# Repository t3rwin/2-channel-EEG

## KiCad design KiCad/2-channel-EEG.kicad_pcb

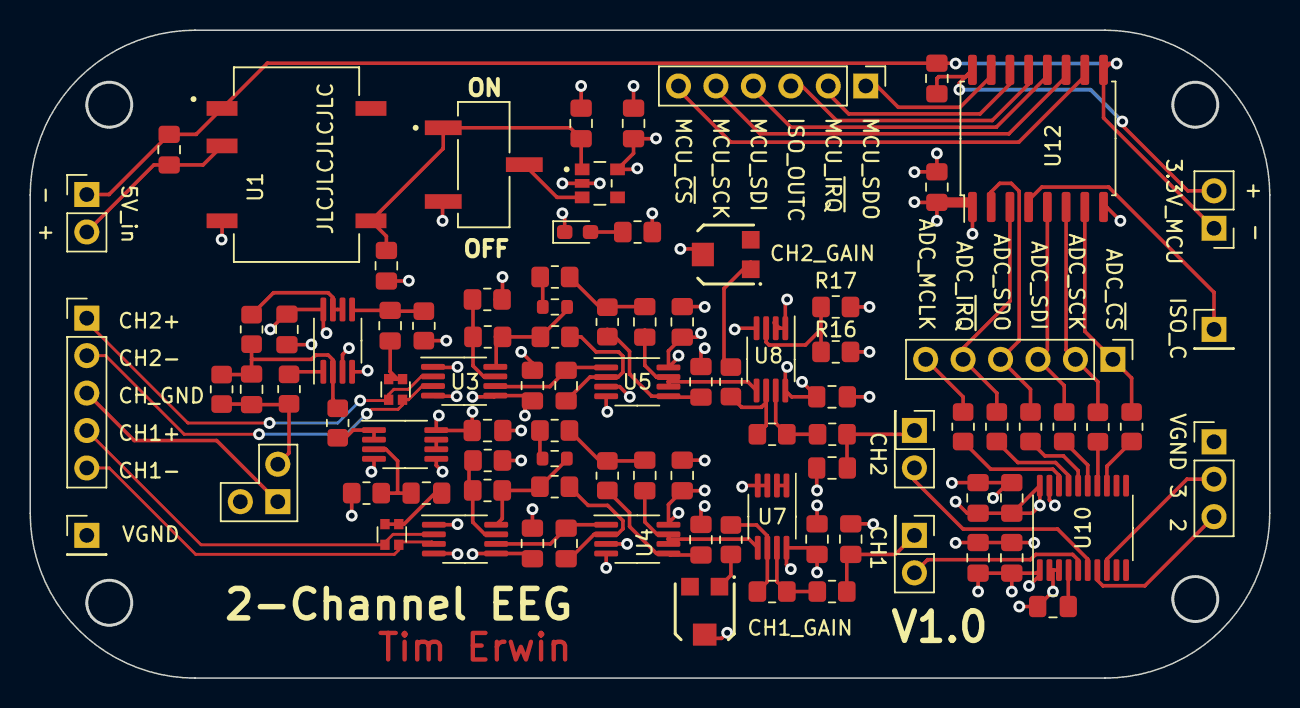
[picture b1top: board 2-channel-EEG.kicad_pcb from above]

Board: 4 copper layers, 84.0 x 43.8 mm, 92 parts (0 on the bottom side), 74 nets.

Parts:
C1: 4.7u; C_0805_2012Metric_Pad1.18x1.45mm_HandSolder
C2, C3, C7, C8, C9, C10, C11, C15, C18, C21, C23, C24, C26, C27, C30: 0.1u; C_0805_2012Metric_Pad1.18x1.45mm_HandSolder
C4, C5, C6, C16, C17, C19, C20, C25: 10u; C_0805_2012Metric_Pad1.18x1.45mm_HandSolder
C12, C28, C29: 1u; C_0805_2012Metric_Pad1.18x1.45mm_HandSolder
C13, C14: 47n; C_0805_2012Metric_Pad1.18x1.45mm_HandSolder
C22: 1n; C_0805_2012Metric_Pad1.18x1.45mm_HandSolder
D1: LED_0603_1608Metric_Pad1.05x0.95mm_HandSolder
J1: Power_Input; PinHeader_1x02_P2.54mm_Vertical
J2: Nucleo_3.3; PinHeader_1x02_P2.54mm_Vertical
J3: Electrode_Input; PinHeader_1x05_P2.54mm_Vertical
J4: GND_select; PinHeader_2x02_P2.54mm_Vertical
J5, J6: Conn_02x01; PinHeader_2x01_P2.54mm_Vertical
J7: VGND; PinHeader_1x01_P2.54mm_Vertical
J8: Conn_01x03; PinHeader_1x03_P2.54mm_Vertical
J9: ADC_Data; PinHeader_1x06_P2.54mm_Vertical
J10: ISO_IN_C; PinHeader_1x01_P2.54mm_Vertical
J11: MCU_Data; PinHeader_1x06_P2.54mm_Vertical
JP1, JP2: SolderJumper_2_Open; R_0603_1608Metric
R1, R3, R21, R30, R31: 1M; R_0805_2012Metric_Pad1.20x1.40mm_HandSolder
R2, R4: 1K; R_0805_2012Metric_Pad1.20x1.40mm_HandSolder
R5, R6: 3M; R_0805_2012Metric_Pad1.20x1.40mm_HandSolder
R7, R8, R9, R10: 56.2k; R_0805_2012Metric_Pad1.20x1.40mm_HandSolder
R11: 510; R_0805_2012Metric_Pad1.20x1.40mm_HandSolder
R12, R13: 1k; R_0805_2012Metric_Pad1.20x1.40mm_HandSolder
R14, R15: 100k; R_0805_2012Metric_Pad1.20x1.40mm_HandSolder
R16, R17, R22, R23: 10k; R_0805_2012Metric_Pad1.20x1.40mm_HandSolder
R18, R19: 100; R_0805_2012Metric_Pad1.20x1.40mm_HandSolder
R20: 0; R_0805_2012Metric_Pad1.20x1.40mm_HandSolder
R24, R25, R26, R27, R28, R29: 10; R_0805_2012Metric_Pad1.20x1.40mm_HandSolder
RN1, RN2: Matched_10K_Resistor_Array_2x; R_Array_Matched_2x0606
RV1, RV2: 10k; TRIM_35WR10KLFTR
SW1: SW_Push_SPDT; SW_JS102011SCQN
U1: PESE1-S5-S5-M-TR; CONV_PESE1-S5-S5-M
U2, U3: AD8237; MSOP-8_3x3mm_P0.65mm
U4, U5, U7, U8, U9, U11: AD8606; MSOP-8_3x3mm_P0.65mm
U6: TCR2EF33; IC_TC4S584F_LF
U10: MCP3562R; TSSOP-20_4.4x6.5mm_P0.65mm
U12: ISO6763-Q1; SOIC-16W_7.5x10.3mm_P1.27mm

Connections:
+3.3V: C2.2, C3.2, C7.2, C8.2, C12.2, C15.1, C18.1, C20.2, C21.2, C23.2, C24.2, C25.2, C26.2, C27.1, R11.2, R16.2, U2.5 (V+), U3.5 (V+), U4.8 (V+), U5.8 (V+), U6.5 (VOUT), U7.8 (V+), U8.8 (V+), U9.8 (V+), U10.1 (AVDD), U10.20 (DVDD), U11.8 (V+), U12.1 (VCC1)
+3V3_nucleo: C30.1, J2.1, U12.16 (VCC2)
+5V: C1.2, J1.1, U1.2 (+VIN)
+5V_iso: C4.2, C9.2, SW1.1 (A), U1.5 (+VOUT), U6.1 (VIN)
/ADC0: J5.2, U10.5 (CH0)
/ADC1: J6.2, U10.6 (CH1)
/ADC2: J8.3, U10.7 (CH2)
/ADC3: J8.2, U10.8 (CH3)
/ADC_MCLK: J9.6, R24.1
/ADC_SCK: J9.2, R28.1, U12.6 (OUTE)
/ADC_SDI: J9.3, R27.1, U12.5 (OUTD)
/ADC_SDO: J9.4, R26.1, U12.2 (INA)
/ADC_~CS: J9.1, R29.1, U12.7 (OUTF)
/ADC_~IRQ: J9.5, R25.1, U12.3 (INB)
/CH1+: J3.4, RN2.3, U2.2 (+)
/CH1-: J3.5, RN2.4, U2.3 (-)
/CH1_AO: C16.2, J5.1, R18.1
/CH2+: J3.1, RN1.3, U3.2 (+)
/CH2-: J3.2, RN1.4, U3.3 (-)
/CH2_AO: C17.2, J6.1, R19.1
/CH_GND: J3.3, J4.1
/Driven_GND: C22.1, J4.2, R20.1, R21.1
/ISO_INC: J10.1, U12.4 (INC)
/ISO_OUTC: J11.3, U12.13 (OUTC)
/LDO_CTRL: SW1.2 (B), U6.3 (CTRL)
/MCU_SCK: J11.5, U12.11 (INE)
/MCU_SDI: J11.4, U12.12 (IND)
/MCU_SDO: J11.1, U12.15 (OUTA)
/MCU_~CS: J11.6, U12.10 (INF)
/MCU_~IRQ: J11.2, U12.14 (OUTB)
/VGND: C13.1, C14.1, C16.1, C17.1, J4.3 (Pin_4), J7.1, J8.1, R2.2, R4.2, R30.1, R31.1, RV1.2, RV2.2, U4.3 (+), U5.3 (+), U8.1, U8.2 (-), U9.3 (+)
GND: C2.1, C3.1, C4.1, C7.1, C8.1, C9.1, C12.1, C15.2, C18.2, C19.2, C20.1, C21.1, C23.1, C24.1, C25.1, C26.1, C27.2, D1.1 (K), R17.1, SW1.3 (C), U1.4 (0V), U2.1 (BW), U2.4 (V-), U3.1 (BW), U3.4 (V-), U4.4 (V-), U5.4 (V-), U6.2 (GND), U7.3 (+), U7.4 (V-), U8.4 (V-), U9.4 (V-), U10.2 (AGND), U10.3 (REFIN-), U10.19 (DGND), U11.4 (V-), U11.5 (+), U12.8 (GND1)
GND1: C1.1, C30.2, J1.2, J2.2, U1.1 (GND), U12.9 (GND2)
unnamed: C10.1, R7.1, R9.2
unnamed: C11.1, R8.1, R10.2
unnamed: C28.2, RN1.1, RN1.2
unnamed: C29.2, RN2.1, RN2.2
unnamed: D1.2 (A), R11.1
unnamed: JP1.1 (A), R1.1, R5.2, U2.8
unnamed: JP1.2 (B), R7.2
unnamed: JP2.1 (A), R3.1, R6.2, U3.8
unnamed: JP2.2 (B), R8.2
unnamed: R12.1, RV1.1
unnamed: R13.1, RV2.1
unnamed: R14.2, R18.2, U7.7
unnamed: R15.2, R19.2, U8.7
unnamed: R20.2, U9.1
unnamed: R1.2, R2.1, U2.7 (FB)
unnamed: C5.1, U2.6 (VREF), U4.1
unnamed: R3.2, R4.1, U3.7 (FB)
unnamed: C6.1, U3.6 (VREF), U5.1
unnamed: C5.2, R5.1, U4.2 (-)
unnamed: C13.2, R9.1, U4.5 (+)
unnamed: C10.2, U4.6 (-), U4.7, U7.5 (+)
unnamed: C6.2, R6.1, U5.2 (-)
unnamed: C14.2, R10.1, U5.5 (+)
unnamed: C11.2, U5.6 (-), U5.7, U8.5 (+)
unnamed: U7.1, U7.2 (-)
unnamed: R12.2, R14.1, U7.6 (-)
unnamed: R16.1, R17.2, U8.3 (+)
unnamed: R13.2, R15.1, U8.6 (-)
unnamed: C22.2, R21.2, R22.2, R23.1, U9.2 (-)
unnamed: C28.1, R30.2, U9.5 (+)
unnamed: R22.1, U9.6 (-), U9.7
unnamed: R24.2, U10.18 (MCLK)
unnamed: C19.1, U10.4 (REFIN+/OUT)
unnamed: R28.2, U10.14 (SCK)
unnamed: R27.2, U10.15 (SDI)
unnamed: R26.2, U10.16 (SDO)
unnamed: R29.2, U10.13 (~CS)
unnamed: R25.2, U10.17 (~IRQ/MDAT)
unnamed: C29.1, R31.2, U11.3 (+)
unnamed: R23.2, U11.1, U11.2 (-)
unnamed: U11.6 (-), U11.7

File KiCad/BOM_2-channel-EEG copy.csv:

Comment,Designator,Footprint,LCSC Part Number
4.7u,C1,0805,C1779
0.1u,"C2, C3, C5, C8, C9, C10, C11, C15, C18, C21, C23, C24, C26, C27, C30",0805,C49678
10u,"C4, C6, C7, C16, C17, C19, C20, C25",0805,C15850
1u,"C12, C28, C29",0805,C28323
47n,"C13, C14",0805,C53134
1n,C22,0805,C46653
LED,D1,0603,C434420
1M,"R1, R3, R20, R29, R30",0805,C17514
1k,"R2,R4,R12, R13",0805,C17513
3M,"R5, R6",0805,C17662
56.2k,"R7, R8, R9, R10",0805,C104412
510,R11,0805,C17734
100k,"R14, R15",0805,C149504
10k,"R16, R17, R21, R22",0805,C17414
100,"R18, R19",0805,C17408
10,"R23, R24, R25, R26, R27, R28",0805,C17415
AD8237ARMZ,"U2, U3",MSOP-8,C578667
AD8606ARMZ-REEL,"U4, U5, U7, U8, U9, U11",MSOP-8,C459905
TCR2EF33,U6,TSOT-25,C843273

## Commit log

2024-01-16 Schematic Updates
    isolation converter, 3.3V LDO, Channel1, Driven GND, Rail Splitter
2024-01-16 Backlink to CADLAB.io has been added.
2024-01-18 separated kicad files from python files
2024-02-05 fixed power connections on U3A, added output filter
2024-04-02 add 2nd channel, start pcb
2024-04-03 PCB updates
2024-04-04 drl filter, additional caps for adc, Rs for adc spi.
2024-04-05 updated DRL and pcb
2024-04-08 added solder jumpers between INA and filter
2024-04-09 fix wrong reference C,R values
2024-04-10 schematic BOM
2024-04-10 add python live processing
2024-04-10 fix .gitignore
2024-04-10 new .gitignore
2024-04-12 final edits before ordering PCB
2024-04-15 py live processing
    live filtering and plotting of pre recorded data
2024-04-17 add fft plotting
2024-04-17 Create UART
2024-04-17 live processing update
2024-04-17 Please delete this file
2024-04-17 added C code folders
2024-04-17 Main and it's prototypes
2024-04-19 fixed missaligned input labels :(
2024-04-22 added smoothing and bar graph
2024-04-23 File contains code that is sent via uart
    receiving the data with minimal processing
2024-04-23 Created a queue data type and showcased basic implementation
2024-04-23 All the C files needed
2024-04-23 import python_rx in plot_power.py and remove global variables in python_rx.py
2024-04-25 upsampling and interpolation of power values
2024-04-25 try with pipes
2024-04-25 fix pipes
2024-04-25 edit .gitignore
2024-05-01 fix interpolation
2024-05-06 one channel live
2024-05-06 2 channels broken
2024-05-06 one channel working
2024-05-08 fixed two channel display
2024-05-15 2 channel
2024-05-15 remove kicad backups
2024-05-29 with demo
2024-05-30 pre-final
2024-06-14 comments
